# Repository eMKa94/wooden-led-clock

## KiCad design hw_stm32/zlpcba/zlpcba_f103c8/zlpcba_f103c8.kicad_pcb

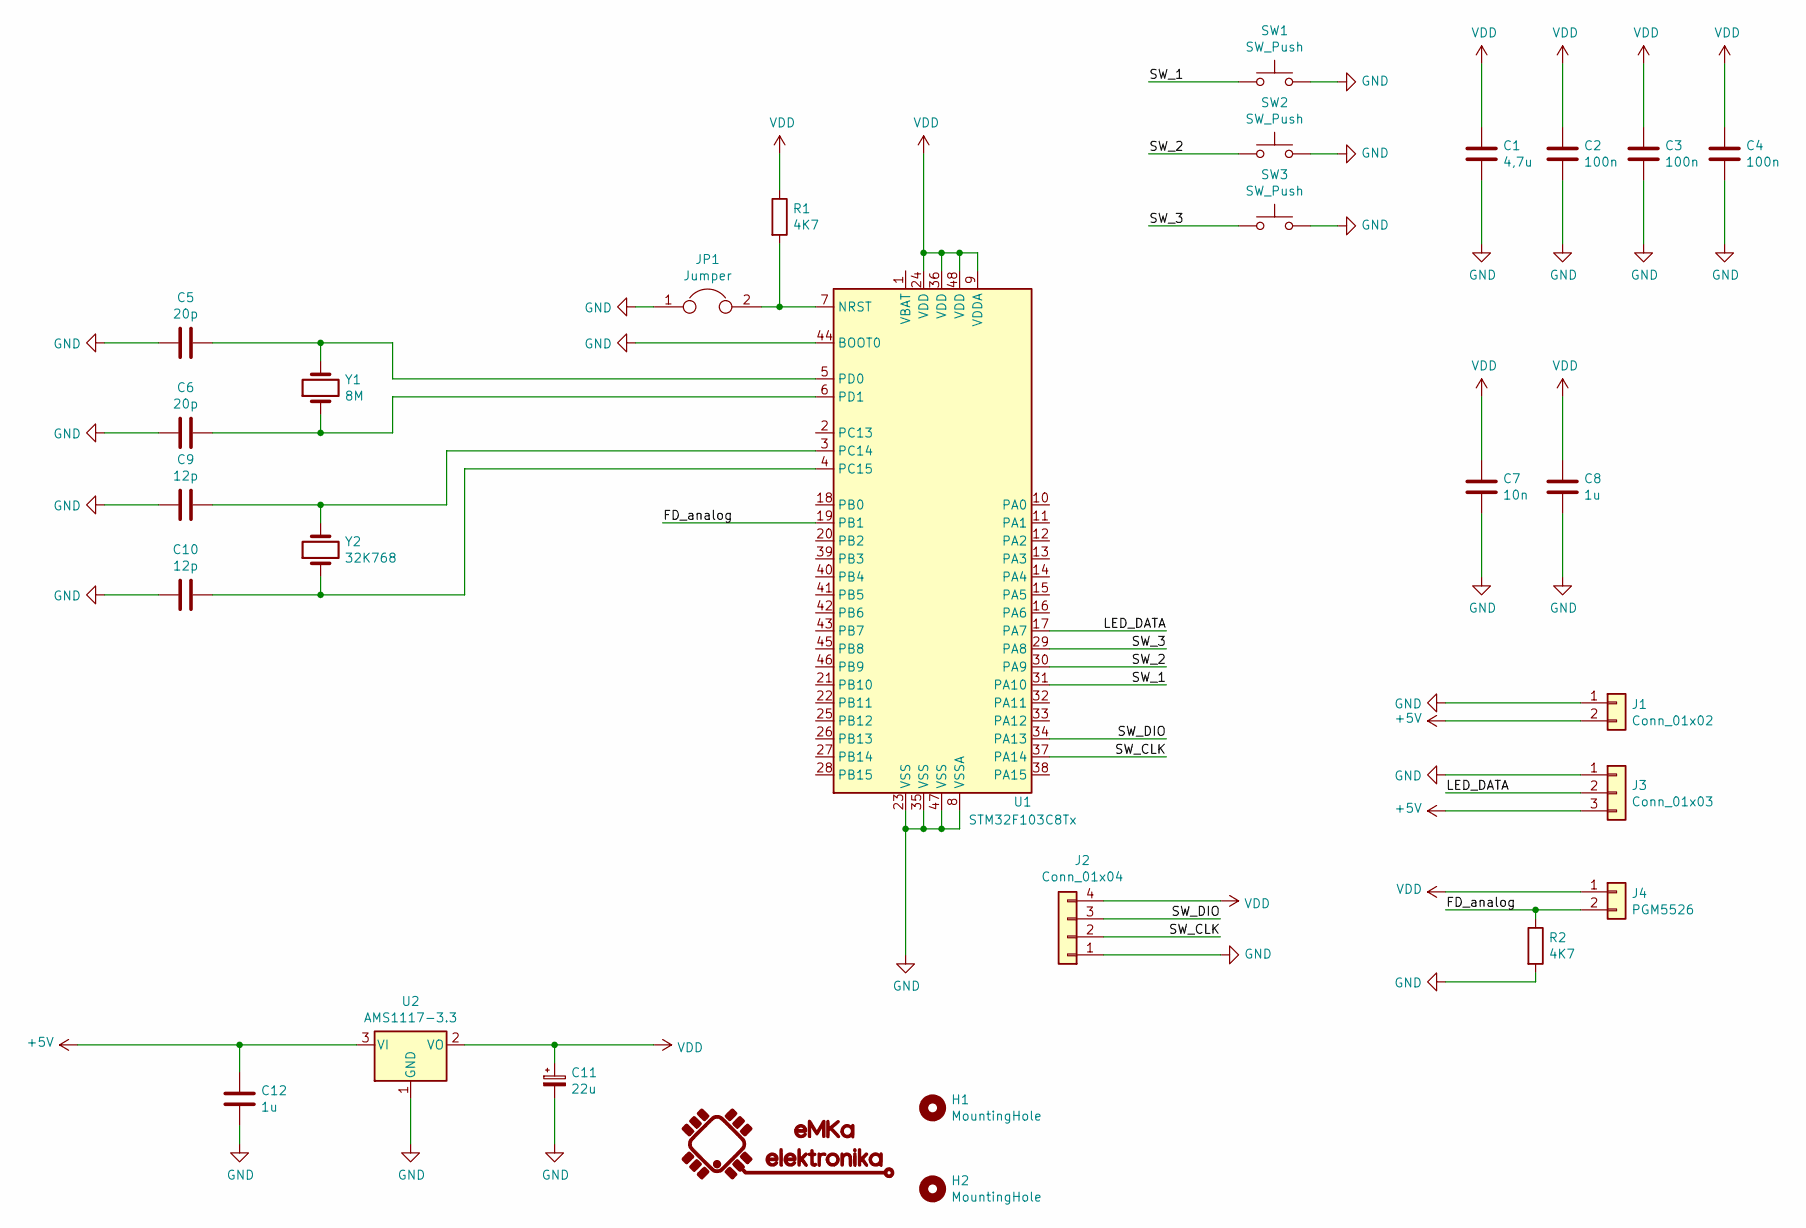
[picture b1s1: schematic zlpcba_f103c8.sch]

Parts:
C1: 4,7u; C_1206_3216Metric
C2, C3, C4: 100n; C_0402_1005Metric
C5, C6: 20p; C_0402_1005Metric
C7: 10n; C_0402_1005Metric
C8, C12: 1u; C_0805_2012Metric
C9, C10: 12p; C_0402_1005Metric
C11: 22u; CP_EIA-3528-21_Kemet-B
G1: eMKa_elektronika_LOGO; emka_logo_male
H1, H2: MountingHole; MountingHole_3.2mm_M3
J1: Conn_01x02; easy_plug_short_x2
J2: Conn_01x04; PinHeader_1x04_P2.54mm_Vertical
J3: Conn_01x03; easy_plug_short_x3
J4: PGM5526; easy_plug_short_x2
JP1: Jumper; SolderJumper-2_P1.3mm_Open_RoundedPad1.0x1.5mm
R1, R2: 4K7; R_0402_1005Metric
SW1, SW2, SW3: SW_Push; SW_SPST_PTS645
U1: STM32F103C8Tx; LQFP-48_7x7mm_P0.5mm
U2: AMS1117-3.3; SOT-223-3_TabPin2
Y1: 8M; Crystal_SMD_5032-2Pin_5.0x3.2mm
Y2: 32K768; Crystal_SMD_3215-2Pin_3.2x1.5mm

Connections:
+5V: C12.1, J1.2, J3.3, U2.3 (VI)
/FD_analog: J4.2, R2.1, U1.19 (PB1)
/LED_DATA: J3.2, U1.17 (PA7)
/SW_1: SW1.1, U1.31 (PA10)
/SW_2: SW2.1, U1.30 (PA9)
/SW_3: SW3.1, U1.29 (PA8)
/SW_CLK: J2.2, U1.37 (PA14)
/SW_DIO: J2.3, U1.34 (PA13)
GND: C1.2, C2.2, C3.2, C4.2, C5.2, C6.2, C7.2, C8.2, C9.2, C10.2, C11.2, C12.2, J1.1, J2.1, J3.1, JP1.1, R2.2, SW1.2, SW2.2, SW3.2, U1.8 (VSSA), U1.23 (VSS), U1.35 (VSS), U1.44 (BOOT0), U1.47 (VSS), U2.1 (GND)
unnamed: C5.1, U1.5 (PD0), Y1.2
unnamed: C6.1, U1.6 (PD1), Y1.1
unnamed: C9.1, U1.3 (PC14), Y2.2
unnamed: C10.1, U1.4 (PC15), Y2.1
unnamed: JP1.2, R1.2, U1.7 (NRST)
VDD: C1.1, C2.1, C3.1, C4.1, C7.1, C8.1, C11.1, J2.4, J4.1, R1.1, U1.9 (VDDA), U1.24 (VDD), U1.36 (VDD), U1.48 (VDD), U2.2 (VO)

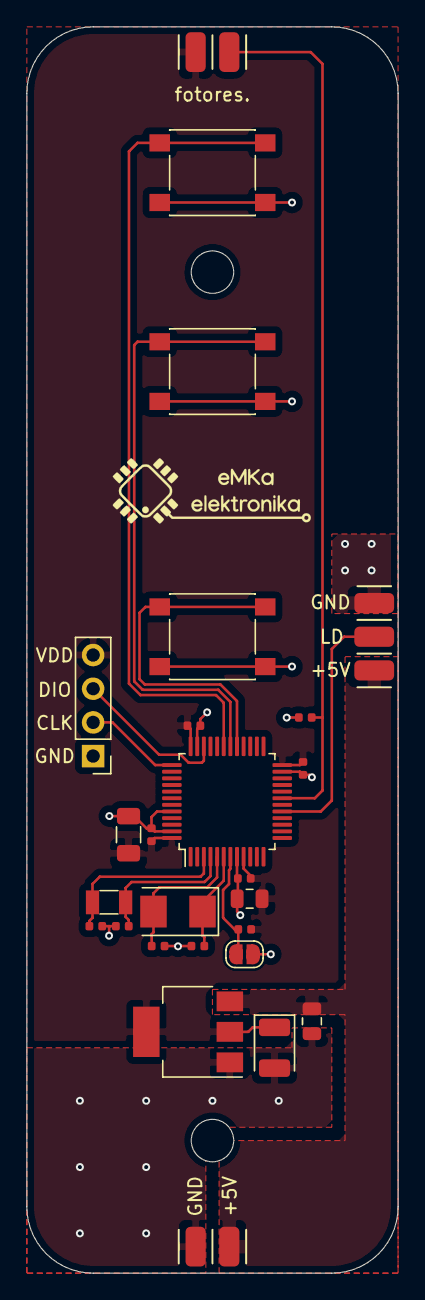
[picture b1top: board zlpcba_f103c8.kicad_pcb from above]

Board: 2 copper layers, 28.0 x 94.0 mm, 29 parts (0 on the bottom side), 15 nets.

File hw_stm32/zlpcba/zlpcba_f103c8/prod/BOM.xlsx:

Comment | Designator | Footprint | LCSC Part #（optional）
SW_Push | SW3,SW2,SW1 | SW_SPST_PTS645
4K7 | R2,R1 | R_0402_1005Metric
AMS1117-3.3 | U2 | SOT-223-3_TabPin2
1u | C12,C8 | C_0805_2012Metric
22u | C11 | CP_EIA-3528-21_Kemet-B
32K768 | Y2 | Crystal_SMD_3215-2Pin_3.2x1.5mm
8M | Y1 | Crystal_SMD_5032-2Pin_5.0x3.2mm
STM32F103C8Tx | U1 | LQFP-48_7x7mm_P0.5mm
Jumper | JP1 | SolderJumper-2_P1.3mm_Open_RoundedPad1.0x1.5mm
12p | C10,C9 | C_0402_1005Metric
10n | C7 | C_0402_1005Metric
20p | C6,C5 | C_0402_1005Metric
100n | C4,C3,C2 | C_0402_1005Metric
4,7u | C1 | C_1206_3216Metric

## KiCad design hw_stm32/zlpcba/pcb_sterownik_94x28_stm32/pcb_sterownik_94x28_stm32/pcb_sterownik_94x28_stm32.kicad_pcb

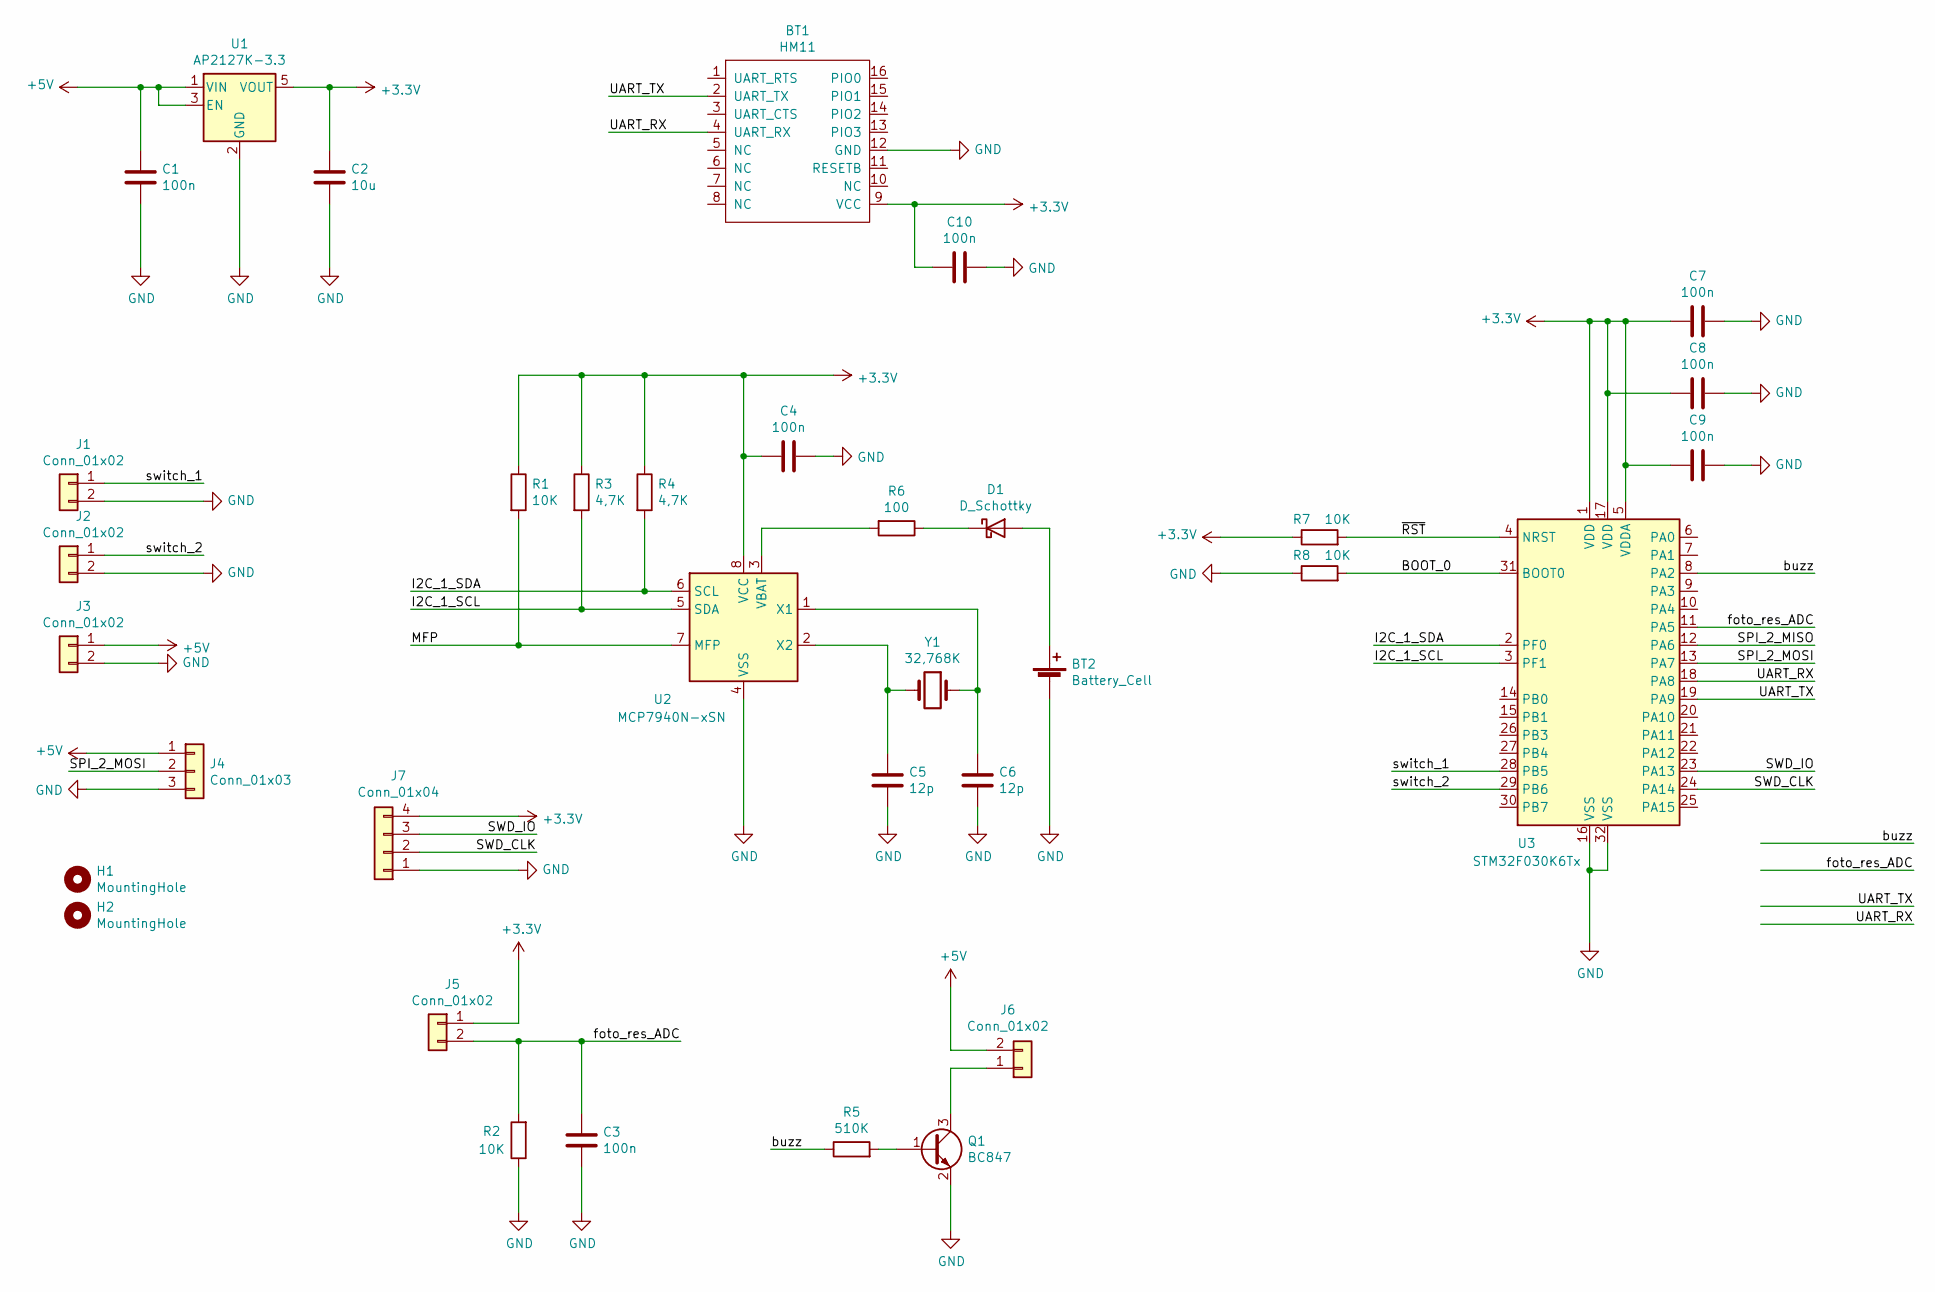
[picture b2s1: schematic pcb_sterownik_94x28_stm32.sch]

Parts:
BT1: HM11; HM-11_BT
BT2: Battery_Cell; BatteryHolder_Keystone_3000_1x12mm
C1, C4, C10: 100n; C_0603_1608Metric
C2: 10u; C_1206_3216Metric
C3, C7, C8, C9: 100n; C_0402_1005Metric
C5, C6: 12p; C_0603_1608Metric
D1: D_Schottky; D_SOD-323
H1, H2: MountingHole; MountingHole_2.5mm
J1, J2, J3, J5, J6: Conn_01x02; PinHeader_1x02_P2.54mm_Vertical
J4: Conn_01x03; PinHeader_1x03_P2.54mm_Vertical
J7: Conn_01x04; PinHeader_1x04_P2.54mm_Vertical
Q1: BC847; SOT-23
R1: 10K; R_0603_1608Metric
R2, R7, R8: 10K; R_0402_1005Metric
R3, R4: 4,7K; R_0603_1608Metric
R5: 510K; R_0603_1608Metric
R6: 100; R_0603_1608Metric
U1: AP2127K-3.3; SOT-23-5
U2: MCP7940N-xSN; SOP-8_3.9x4.9mm_P1.27mm
U3: STM32F030K6Tx; LQFP-32_7x7mm_P0.8mm
Y1: 32,768K; Crystal_AT310_D3.0mm_L10.0mm_Horizontal

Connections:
+3V3: BT1.9 (VCC), C2.2, C4.1, C7.2, C8.2, C9.2, C10.1, J5.1, J7.4, R1.1, R3.1, R4.1, R7.1, U1.5 (VOUT), U2.8 (VCC), U3.1 (VDD), U3.5 (VDDA), U3.17 (VDD)
+5V: C1.2, J3.1, J4.1, J6.2, U1.1 (VIN), U1.3 (EN)
/BOOT_0: R8.2, U3.31 (BOOT0)
/I2C_1_SCL: R3.2, U2.5 (SDA), U3.3 (PF1)
/I2C_1_SDA: R4.2, U2.6 (SCL), U3.2 (PF0)
/MFP: R1.2, U2.7 (MFP)
/SPI_2_MISO: U3.12 (PA6)
/SPI_2_MOSI: J4.2, U3.13 (PA7)
/SWD_CLK: J7.2, U3.24 (PA14)
/SWD_IO: J7.3, U3.23 (PA13)
/UART_RX: BT1.4 (UART_RX), U3.18 (PA8)
/UART_TX: BT1.2 (UART_TX), U3.19 (PA9)
/buzz: R5.1, U3.8 (PA2)
/foto_res_ADC: C3.2, J5.2, R2.2, U3.11 (PA5)
/switch_1: J1.1, U3.28 (PB5)
/switch_2: J2.1, U3.29 (PB6)
/~RST: R7.2, U3.4 (NRST)
GND: BT1.12 (GND), BT2.2 (-), C1.1, C2.1, C3.1, C4.2, C5.1, C6.1, C7.1, C8.1, C9.1, C10.2, J1.2, J2.2, J3.2, J4.3, J7.1, Q1.2 (E), R2.1, R8.1, U1.2 (GND), U2.4 (VSS), U3.16 (VSS), U3.32 (VSS)
unnamed: BT2.1 (+), D1.2 (A)
unnamed: C5.2, U2.2 (X2), Y1.2
unnamed: C6.2, U2.1 (X1), Y1.1
unnamed: D1.1 (K), R6.1
unnamed: J6.1, Q1.3 (C)
unnamed: Q1.1 (B), R5.2
unnamed: R6.2, U2.3 (VBAT)

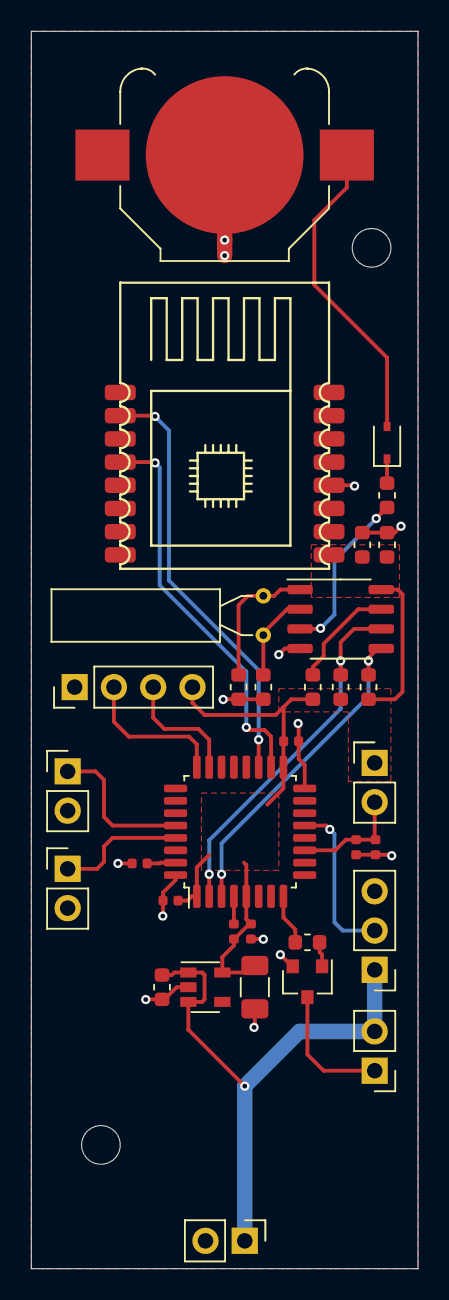
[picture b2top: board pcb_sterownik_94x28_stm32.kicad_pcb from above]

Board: 2 copper layers, 25.0 x 80.0 mm, 35 parts (0 on the bottom side), 24 nets.

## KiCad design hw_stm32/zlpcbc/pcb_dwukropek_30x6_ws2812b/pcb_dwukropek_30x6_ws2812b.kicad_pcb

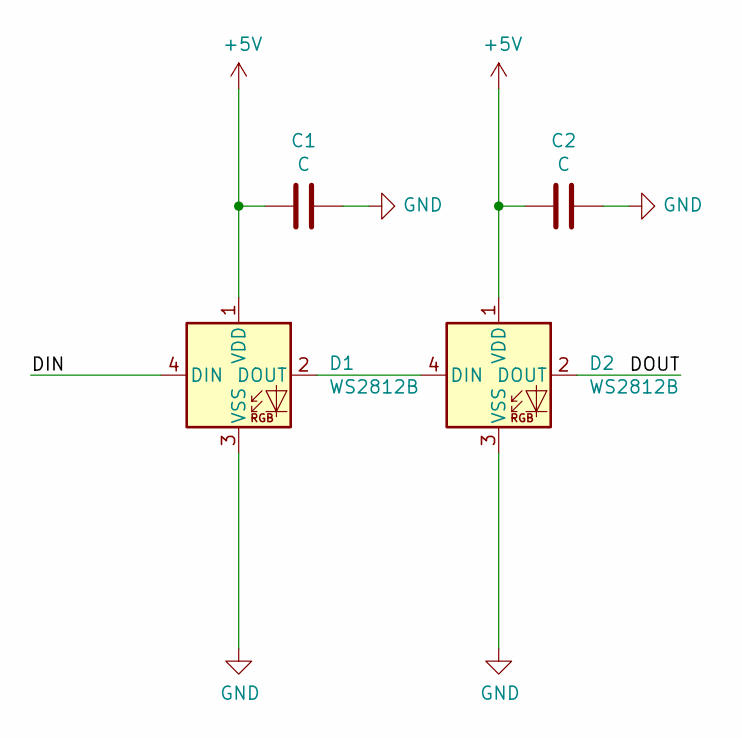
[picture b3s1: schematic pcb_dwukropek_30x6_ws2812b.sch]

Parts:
C1, C2: C; C_0603_1608Metric
D1, D2: WS2812B; LED_WS2812B_PLCC4_5.0x5.0mm_P3.2mm

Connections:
+5V: C1.2, C2.2, D1.1 (VDD), D2.1 (VDD)
/DIN: D1.4 (DIN)
/DOUT: D2.2 (DOUT)
GND: C1.1, C2.1, D1.3 (VSS), D2.3 (VSS)
unnamed: D1.2 (DOUT), D2.4 (DIN)

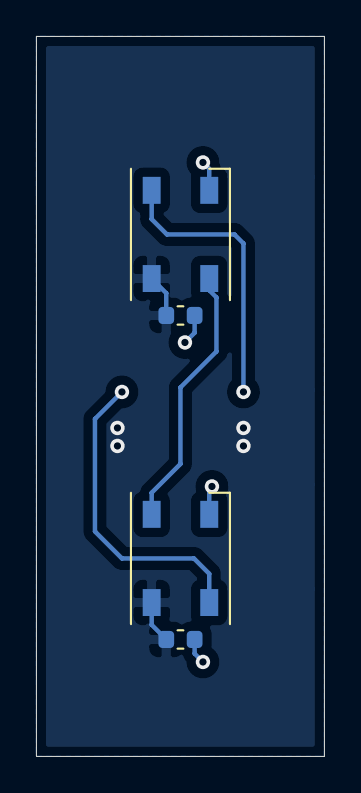
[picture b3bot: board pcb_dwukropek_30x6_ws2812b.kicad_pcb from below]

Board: 2 copper layers, 16.0 x 40.0 mm, 4 parts (4 on the bottom side), 3 nets.

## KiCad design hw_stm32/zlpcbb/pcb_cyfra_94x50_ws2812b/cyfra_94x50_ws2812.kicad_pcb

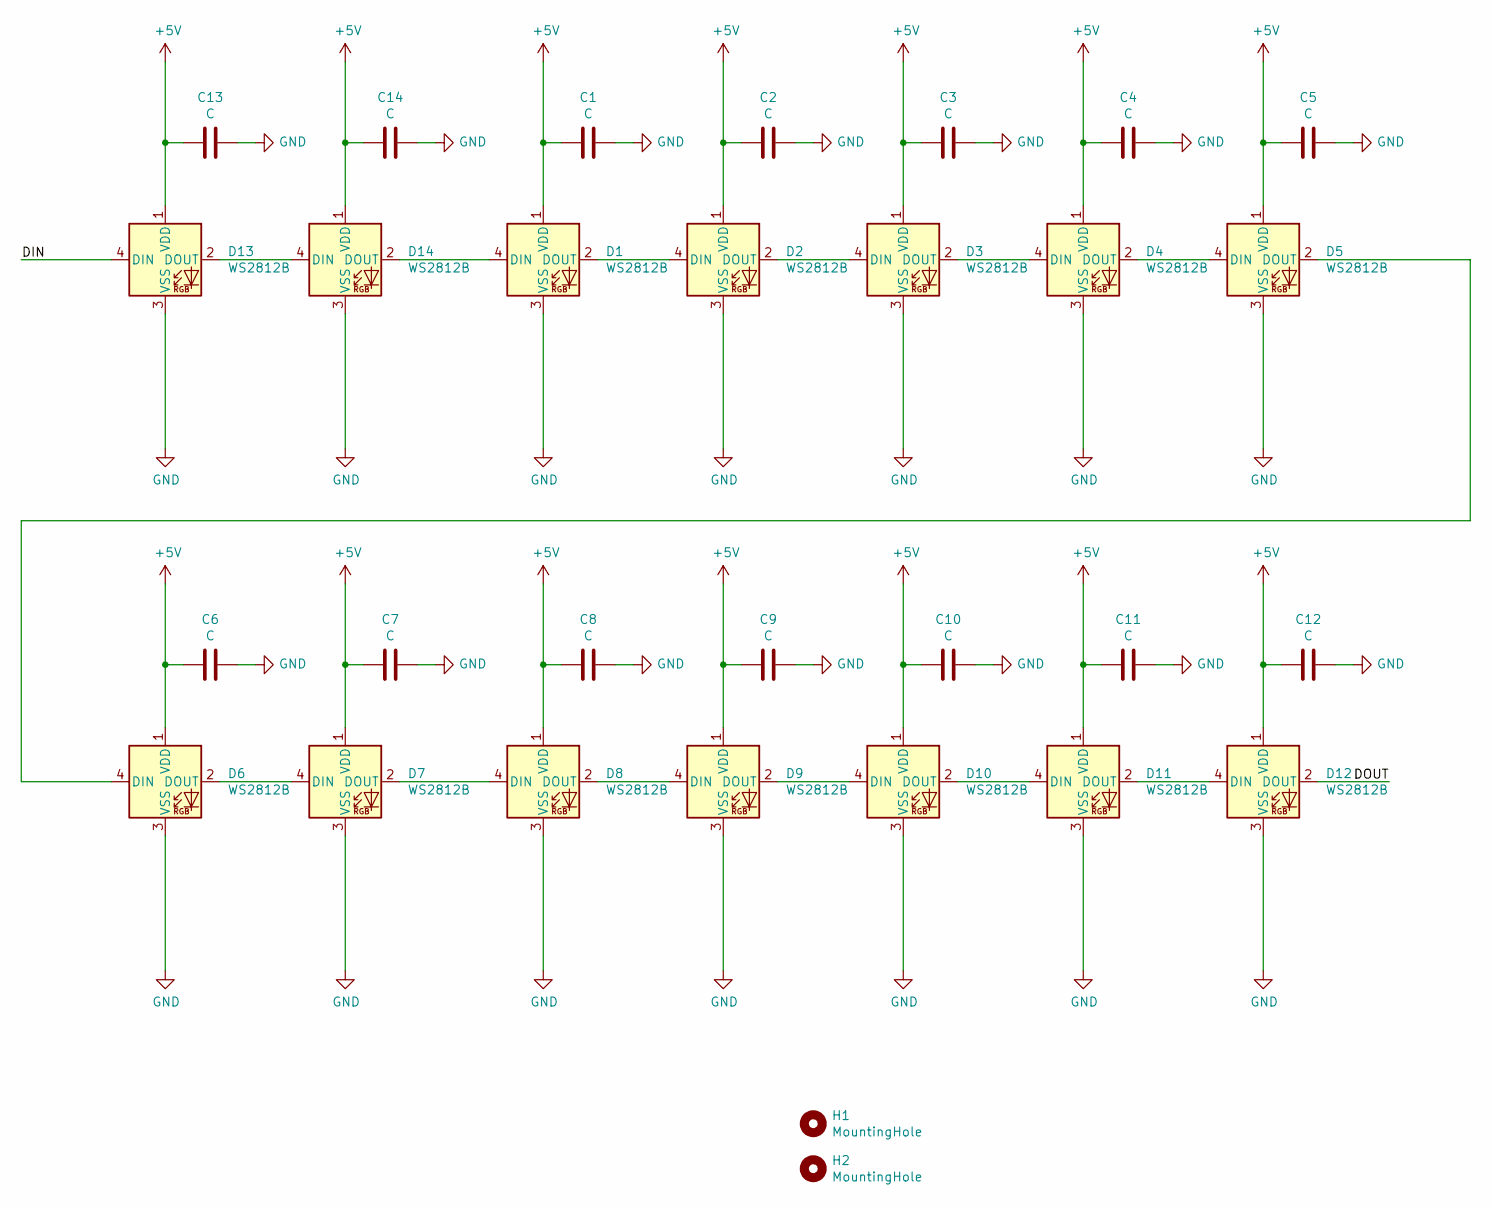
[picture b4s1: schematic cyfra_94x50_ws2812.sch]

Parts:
C1, C2, C3, C4, C5, C6, C7, C8, C9, C10, C11, C12, C13, C14: C; C_0603_1608Metric
D1, D2, D3, D4, D5, D6, D7, D8, D9, D10, D11, D12, D13, D14: WS2812B; LED_WS2812B_PLCC4_5.0x5.0mm_P3.2mm
H1, H2: MountingHole; MountingHole_3.2mm_M3

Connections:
+5V: C1.2, C2.2, C3.2, C4.2, C5.2, C6.2, C7.2, C8.2, C9.2, C10.2, C11.2, C12.2, C13.2, C14.2, D1.1 (VDD), D2.1 (VDD), D3.1 (VDD), D4.1 (VDD), D5.1 (VDD), D6.1 (VDD), D7.1 (VDD), D8.1 (VDD), D9.1 (VDD), D10.1 (VDD), D11.1 (VDD), D12.1 (VDD), D13.1 (VDD), D14.1 (VDD)
/DIN: D13.4 (DIN)
/DOUT: D12.2 (DOUT)
GND: C1.1, C2.1, C3.1, C4.1, C5.1, C6.1, C7.1, C8.1, C9.1, C10.1, C11.1, C12.1, C13.1, C14.1, D1.3 (VSS), D2.3 (VSS), D3.3 (VSS), D4.3 (VSS), D5.3 (VSS), D6.3 (VSS), D7.3 (VSS), D8.3 (VSS), D9.3 (VSS), D10.3 (VSS), D11.3 (VSS), D12.3 (VSS), D13.3 (VSS), D14.3 (VSS)
unnamed: D1.2 (DOUT), D2.4 (DIN)
unnamed: D1.4 (DIN), D14.2 (DOUT)
unnamed: D2.2 (DOUT), D3.4 (DIN)
unnamed: D3.2 (DOUT), D4.4 (DIN)
unnamed: D4.2 (DOUT), D5.4 (DIN)
unnamed: D5.2 (DOUT), D6.4 (DIN)
unnamed: D6.2 (DOUT), D7.4 (DIN)
unnamed: D7.2 (DOUT), D8.4 (DIN)
unnamed: D8.2 (DOUT), D9.4 (DIN)
unnamed: D10.2 (DOUT), D11.4 (DIN)
unnamed: D9.2 (DOUT), D10.4 (DIN)
unnamed: D11.2 (DOUT), D12.4 (DIN)
unnamed: D13.2 (DOUT), D14.4 (DIN)

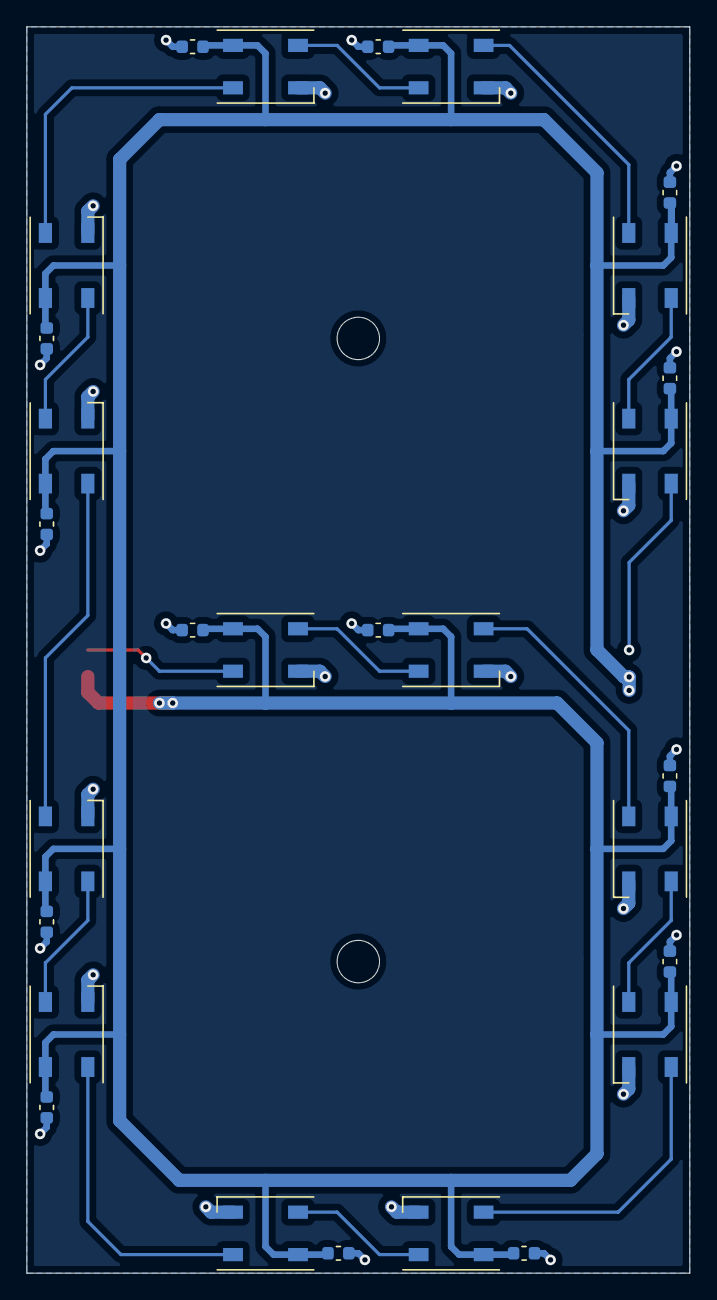
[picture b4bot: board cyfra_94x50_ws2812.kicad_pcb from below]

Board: 2 copper layers, 50.0 x 94.0 mm, 30 parts (28 on the bottom side), 15 nets.

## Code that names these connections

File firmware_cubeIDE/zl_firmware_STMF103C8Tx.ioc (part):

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Mcu.Name=STM32F103C(8-B)Tx
Mcu.Package=LQFP48
Mcu.UserName=STM32F103C8Tx
PA13.Mode=Serial_Wire
PA13.Signal=SYS_JTMS-SWDIO
PA14.Mode=Serial_Wire
PA14.Signal=SYS_JTCK-SWCLK
PA5.Mode=TX_Only_Simplex_Unidirect_Master
PA5.Signal=SPI1_SCK
PA7.Mode=TX_Only_Simplex_Unidirect_Master
PA7.Signal=SPI1_MOSI
PB1.Signal=ADCx_IN9
PB10.GPIOParameters=GPIO_PuPd
PB10.GPIO_PuPd=GPIO_PULLUP
PB10.Signal=GPIO_Input
PB11.GPIOParameters=GPIO_PuPd
PB11.GPIO_PuPd=GPIO_PULLUP
PB11.Signal=GPIO_Input
PC13-TAMPER-RTC.Signal=GPIO_Output
PC14-OSC32_IN.Mode=LSE-External-Oscillator
PC14-OSC32_IN.Signal=RCC_OSC32_IN
PC15-OSC32_OUT.Mode=LSE-External-Oscillator
PC15-OSC32_OUT.Signal=RCC_OSC32_OUT
PD0-OSC_IN.Mode=HSE-External-Oscillator
PD0-OSC_IN.Signal=RCC_OSC_IN
PD1-OSC_OUT.Mode=HSE-External-Oscillator
PD1-OSC_OUT.Signal=RCC_OSC_OUT
RCC.SYSCLKFreq_VALUE=48000000
RCC.SYSCLKSource=RCC_SYSCLKSOURCE_PLLCLK
board=custom

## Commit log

2021-08-17 project files add
